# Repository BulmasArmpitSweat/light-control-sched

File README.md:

# light-control-sched

Code for a simple IoT device to control a light on a schedule, using NTP, and configurable with a Captive Portal.

Please keep in mind that this code is incomplete, and hardly builds as it stands, so use at your own risk.

To download FreeRTOS, enter the cloned repo, and enter the command `git submodule init`

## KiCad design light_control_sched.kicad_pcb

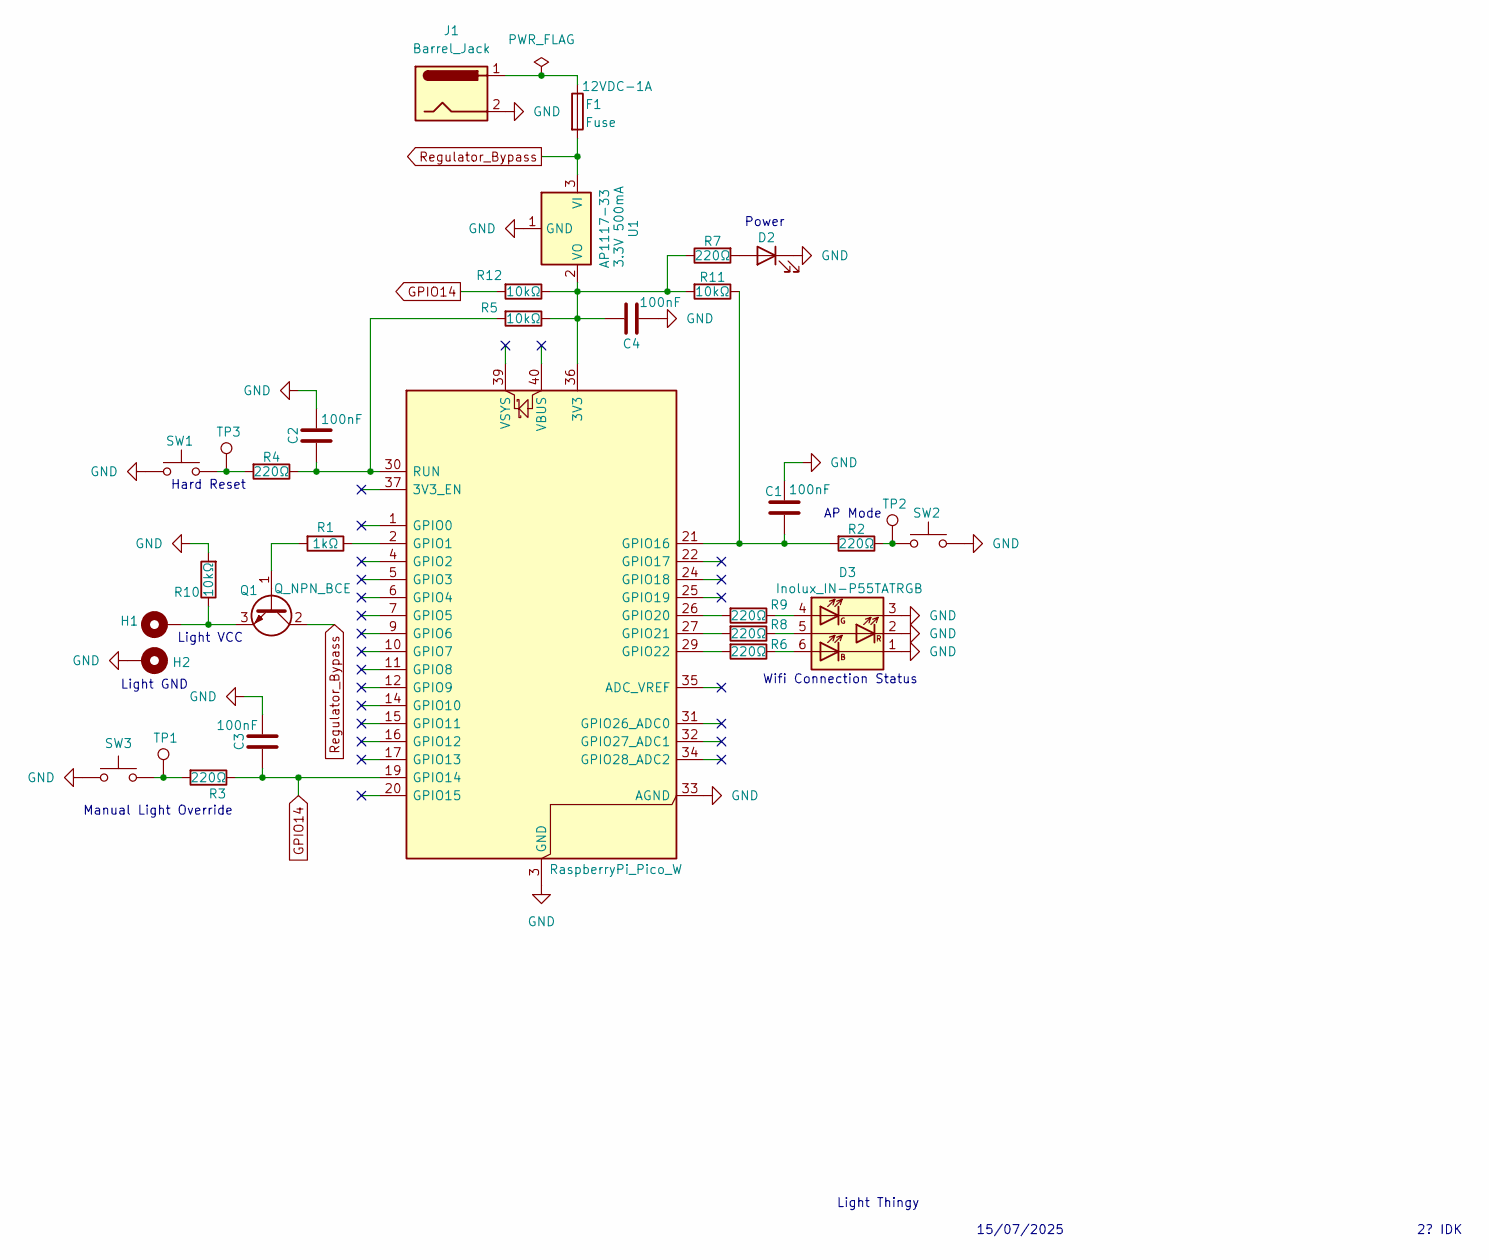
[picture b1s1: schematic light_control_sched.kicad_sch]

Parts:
A1: RaspberryPi_Pico_W; RaspberryPi_Pico_W_SMD_HandSolder
C1, C2, C3, C4: C; C_0805_2012Metric
D2: LED; LED_0805_2012Metric
D3: Inolux_IN-P55TATRGB; LED_Inolux_IN-P55TATRGB_PLCC6_5.0x5.5mm_P1.8mm
F1: Fuse; Fuse_0402_1005Metric; Rating 12VDC-1A
H1, H2: MountingHole_Pad; MountingHole_2.2mm_M2_DIN965_Pad
J1: Barrel_Jack; BarrelJack_GCT_DCJ200-10-A_Horizontal
Q1: Q_NPN_BCE; SOT-323_SC-70_Handsoldering
R1, R2, R3, R4, R5, R6, R7, R8, R9, R10, R11, R12: R; R_0603_1608Metric_Pad0.98x0.95mm_HandSolder
SW1, SW2, SW3: SW_Push; SW_SPST_TL3342
TP1, TP2, TP3: TestPoint; TestPoint_Pad_D1.5mm
U1: AP1117-33; SOT-223-3_TabPin2; Output Voltage 3.3V 500mA

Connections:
GND: A1.3 (GND), A1.8 (GND), A1.13 (GND), A1.18 (GND), A1.23 (GND), A1.28 (GND), A1.33 (AGND), A1.38 (GND), C1.1, C2.2, C3.2, C4.1, D2.1 (K), D3.1 (KB), D3.2 (KR), D3.3 (KG), H2.1, J1.2, R10.2, SW1.2, SW2.1, SW3.2, U1.1 (GND)
GPIO14: A1.19 (GPIO14), C3.1, R3.1, R12.2
unnamed: A1.36 (3V3), C4.2, R5.1, R7.1, R11.2, R12.1, U1.2 (VO)
unnamed: A1.2 (GPIO1), R1.1
unnamed: A1.21 (GPIO16), C1.2, R2.2, R11.1
unnamed: A1.26 (GPIO20), R9.2
unnamed: A1.27 (GPIO21), R8.2
unnamed: A1.29 (GPIO22), R6.2
unnamed: A1.30 (RUN), C2.1, R4.1, R5.2
unnamed: D2.2 (A), R7.2
unnamed: D3.6 (AB), R6.1
unnamed: D3.4 (AG), R9.1
unnamed: D3.5 (AR), R8.1
unnamed: F1.1, J1.1
unnamed: Q1.1 (B), R1.2
unnamed: H1.1, Q1.3 (E), R10.1
unnamed: R2.1, SW2.2, TP2.1
unnamed: R3.2, SW3.1, TP1.1
unnamed: R4.2, SW1.1, TP3.1
Regulator_Bypass: F1.2, Q1.2 (C), U1.3 (VI)

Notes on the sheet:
Wifi Connection Status
Manual Light Override
Power
AP Mode
Light VCC
Hard Reset
Light Thingy
Light GND
15/07/2025
2? IDK

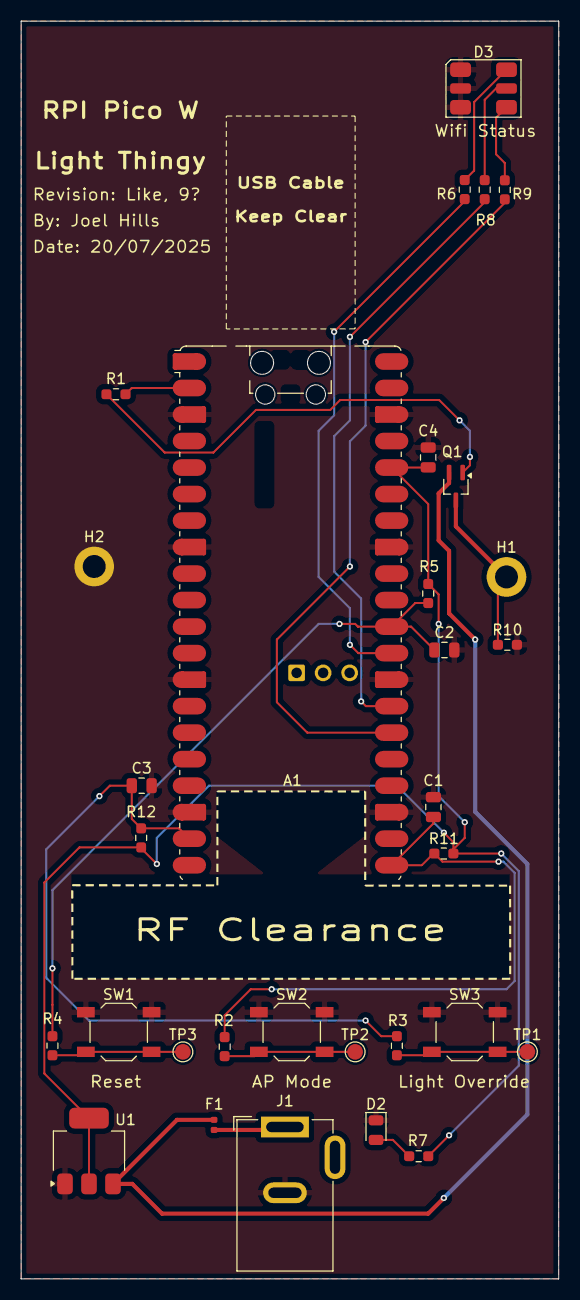
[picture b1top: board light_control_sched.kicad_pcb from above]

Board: 2 copper layers, 51.5 x 120.5 mm, 31 parts (0 on the bottom side), 20 nets.

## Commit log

2025-07-21 Added main repo via upload
2025-07-21 Added PCB via upload
